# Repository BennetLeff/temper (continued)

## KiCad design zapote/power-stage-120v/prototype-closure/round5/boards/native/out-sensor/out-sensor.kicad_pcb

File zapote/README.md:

# Zapote

**Board checks:** [ERC, DRC and layout command index](CHECKS.md), or
`make -C zapote help`. Includes native current analysis, before/after comparisons,
Rust owners, test evidence, and the current integration/CI checkpoint.

> **Scope on `main` (landed 2026-10-08).** Five maintained units — RTD, current-sense,
> thermal-sense, interlock, gate-drive — plus `power-stage-120v` and the inverter
> measurement framework (superseded by the 120 V stage's own validation plan; see
> `inverter/U3-MEASUREMENT-READINESS.md`). The Rev38 PFC power entry, the voltage-sense unit, the
> PFC-board bridge/shunt FEM and cooling studies, and their crate modules are
> archived at tags `archive/rev38-power-entry-2026-09-25` and
> `archive/zapote-coil-intake-2026-09-25` (see `docs/archive/REV38.md`). Unit
> evidence runs not read by a check also stay in those tags; a unit
> `ACCEPTANCE.md` path that is absent here resolves there. Bulk solver output
> (`*.gz`, `*.npz`, files over 5 MB) is in release `zapote-evidence-2026-10-08`;
> `python3 zapote/tools/evidence_archive.py fetch` restores it in place.

Zapote is Temper's agent engineering subproject centered on a large Rust
validation suite. The working Python/KiCad editing adapter stays in use.

It shares Temper's product inputs and copies needed existing Rust validators
into focused packages such as `zapote-drc` and `zapote-erc`, retaining tests and
provenance. The agent makes placement and routing decisions; Zapote supplies
explicit board edits, engineering feedback, memory, and recorded execution.
See [ARCHITECTURE.md](ARCHITECTURE.md) for package boundaries and
[VALIDATION.md](VALIDATION.md) for the board-validation objective and coverage
ambition. Replacing the Python adapter is deferred.

The [cooker delivery roadmap](https://github.com/BennetLeff/temper/blob/archive/zapote-coil-intake-2026-09-25/docs/plans/2026-09-10-1627-zapote-cooker-roadmap-plan.md)
sets the order from standalone buck/MCU units through the complete routed board and
physical bring-up. Each milestone adds cooker circuitry, Rust validation coverage
and reusable engineering lessons; implementation detail is added as it approaches.

## Current status

Zapote has a standalone Rust workspace with core, DRC, ERC and harness packages.
The [RTD unit](rtd/unit/ACCEPTANCE.md) exercises the source-to-board flow, and
[model qualification](rtd/model-correctness/README.md) checks the meaning of its
passive-network certificates. Device applicability and brownout timing remain
INDETERMINATE; physical tests are NOT RUN.

The [standalone current-sense / primary OCP unit](current-sense/README.md)
adds a separately compiled Atopile source, routed native PCB, corrected
transformer land pattern, bounded electrical model and Rust source/geometry
checks. Its acceptance record separates digital verification from unrun
physical qualification and procurement gaps.

The [standalone voltage-sense / OVP unit](https://github.com/BennetLeff/temper/blob/archive/zapote-coil-intake-2026-09-25/zapote/voltage-sense/README.md) adds the next separately compiled, routed unit, a corrected ADC divider, source-derived electrical checks and saved-document consistency controls. Its digital construction passes while qualification remains explicit.

The [standalone thermal unit](thermal-sense/README.md) adds two external-NTC channels, loaded-feedback trip/release modeling, exact connectivity controls and a routed native PCB. Rev B adds conditional open-wire detection; physical qualification remains separate.

The [isolated gate-drive unit](gate-drive/README.md) has a routed 100 × 80 mm candidate with clean native ERC/DRC and passing Rust construction checks; physical qualification is unrun. The [active PFC power-entry unit](https://github.com/BennetLeff/temper/blob/archive/zapote-coil-intake-2026-09-25/zapote/power-entry/README.md) preserves the 1,800 W nominal AC-input target. Its 54-component, 230 × 210 mm candidate is routed with zero native ERC/DRC findings or unconnected nets and seven passing Rust construction findings. Qualification remains INDETERMINATE. See the [two-board demo](https://github.com/BennetLeff/temper/blob/archive/zapote-coil-intake-2026-09-25/zapote/demo-gate-power/index.html).

The [Rust coverage inventory](validation/inventory-2026-09-12.json) maps Temper donors to Zapote,
lists the checks recorded for each maintained unit, and orders the next ports.
The `zapote-board` CLI checks physical stackup only. The [check index](CHECKS.md)
lists the separate native layout/current and unit electrical-validation commands.

[Engineering memory](https://github.com/BennetLeff/temper/blob/archive/zapote-coil-intake-2026-09-25/zapote/skills/README.md) connects reviewed, versioned lessons to
construction inputs through Rust selection and a thin process transport (the catalog and
Python transport are archived; the Rust policy remains in `zapote-harness`). The
native KiCad adapters live in `harness-lab/`, the generators in `tools/generators/`
and the atopile base library in `elec-base/src`. The old Python
migration outline is superseded by [MIGRATION.md](https://github.com/BennetLeff/temper/blob/archive/zapote-coil-intake-2026-09-25/zapote/MIGRATION.md).

The [Gmsh + Elmer thermal backend](https://github.com/BennetLeff/temper/blob/archive/zapote-coil-intake-2026-09-25/zapote/thermal/README.md) adds a separate external
electrothermal reference path, orchestrated and checked in Rust. Its copper-bar
benchmark establishes solver setup; it does not qualify the power-entry necks
or replace existing board findings.

## Layout

| Path | Purpose |
|---|---|
| `project.toml` | Zapote identity and shared Temper resource map |
| `AGENTS.md` | Local operating rules for work in this project |
| `Makefile` | Rust build/test and common saved-board gates |
| `CHECKS.md` | Check discovery: commands, scope, code owners, evidence and CI status |
| `layout-quality/` | Native geometry/current feedback and supplied-model check catalog |
| `Cargo.toml`, `packages/` | Rust workspace, validators and harness |
| `ports.toml` | Donor hashes, copied tests and extraction changes |
| `validation/` | Dated donor inventory, per-unit coverage and next-port sequence |
| `thermal/` | Gmsh + Elmer backend scope, native installation and reference evidence |
| `ARCHITECTURE.md` | Rust package ownership and agent/validator contract |
| `experiments/` | Experiment definitions and frozen inputs |
| `skills/` | Versioned agent skills and learned artifacts |
| `artifacts/` | Durable evidence manifests and local artifact indexes |
| `runs/` | Git-ignored runtime output |
| `evidence-archive.json` | Manifest of bulk evidence held in release assets; restore with `tools/evidence_archive.py fetch` |
| `docs/` | Design, migration, and operating notes |

## Commands

```sh
make -C zapote setup
make -C zapote help
make -C zapote check
make -C zapote build
```

`setup` checks Rust workspace metadata, `build` builds its binaries/examples,
and `check` runs release Rust tests, native 120 V layout/current analysis, then
the five-unit acceptance runner. Native commands need the KiCad runtimes listed
in [CHECKS.md](CHECKS.md). `check-boards` runs stackup checks only.

Check any new board with `make -C zapote board-check BOARD=/absolute/path/to/board.kicad_pcb`.
The `zapote-board` Rust CLI reads the actual PCB bytes, hashes them and runs
`DRC.BOARD.STACKUP`; its pass is not a substitute for unit electrical checks
or native ERC/DRC. Register new maintained unit paths in `UNIT_BOARDS` before
acceptance. Historical/frozen artifacts are not modified by these commands.
Legacy buck `qualify-buck` and `engineering` commands remain explicitly delegated.

## Direction

Zapote is not another PCB optimizer. It is the harness layer that makes agent
behavior measurable, repeatable, inspectable, and improvable across Temper's
engineering domains. See `MIGRATION.md` for the planned boundary and the
current source-of-truth decisions.

The [standalone interlock](interlock/README.md) adds seven fault inputs, watchdog/liveness gating and a stateful reset latch. Its source-driven Rust checks evaluate 4,096 gate/state/clock combinations and reject physical connectivity and model mutations. Sensor-liveness production and receiver behavior remain integration obligations.

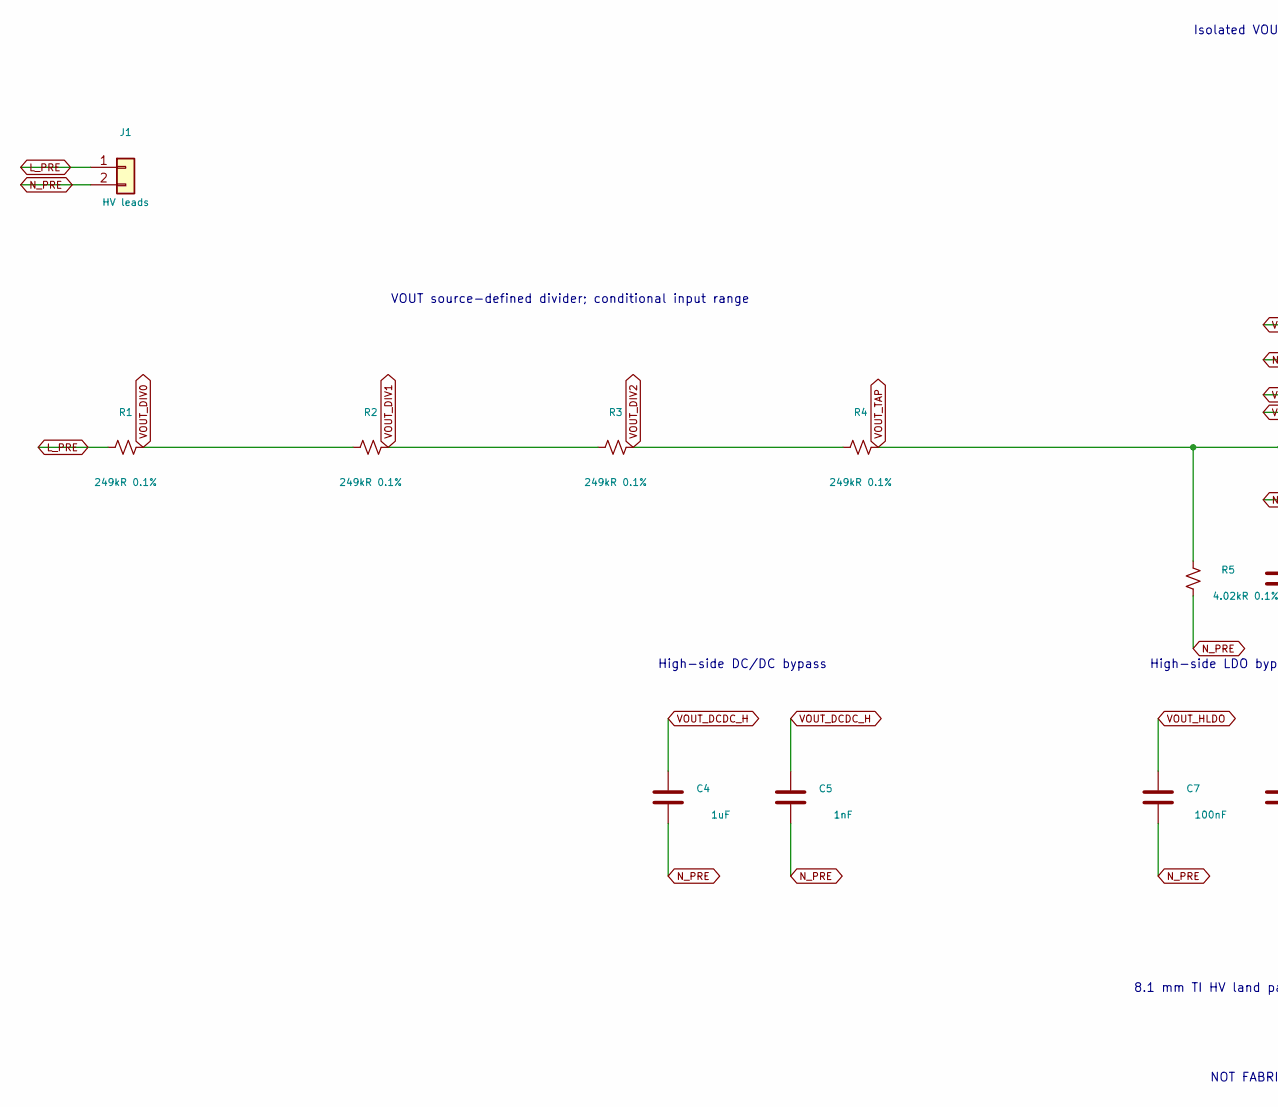
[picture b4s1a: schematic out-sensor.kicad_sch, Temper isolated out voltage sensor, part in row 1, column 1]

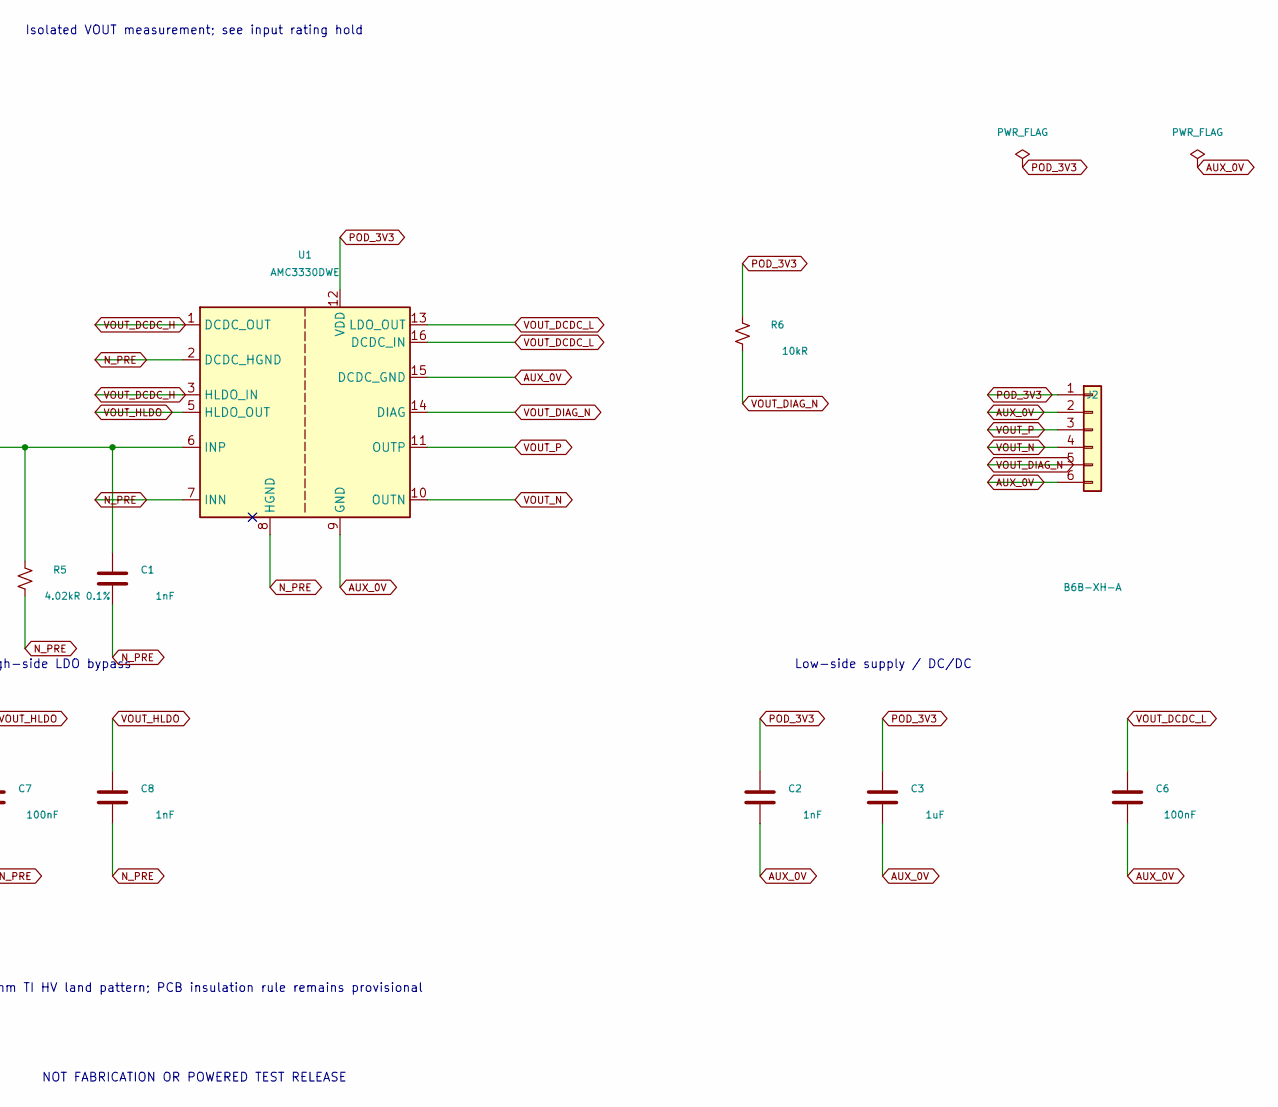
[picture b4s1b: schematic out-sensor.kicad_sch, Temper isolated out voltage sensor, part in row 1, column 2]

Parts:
C1: 1nF; C_0603_1608Metric; MPN 1nF C0603C102J5GACTU
C2: 1nF; C_1206_3216Metric; MPN 1nF 12065C102KAT2A
C3: 1uF; C_1206_3216Metric; MPN 1uF 12063C105KAT2A
C4: 1uF; C_0603_1608Metric; MPN 1uF CGA3E1X7R1E105K080AC
C5, C8: 1nF; C_0603_1608Metric; MPN 1nF C0603C102K5RACTU
C6, C7: 100nF; C_0603_1608Metric; MPN 100nF C0603C104K5RACAUTO
J1: HV leads; HV_WirePair_P25; MPN HV_SOLDER_LEADS_WITH_EXTERNAL_STRAIN_RE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
J2: B6B-XH-A; JST_XH_B6B-XH-A_1x06_P2.50mm_Vertical; MPN B6B-XH-A(LF)(SN)
R1, R2, R3, R4: 249kR 0.1%; R_1206_3216Metric; MPN TNPW1206249KBEEA 249kR 0.1%
R5: 4.02kR 0.1%; R_1206_3216Metric; MPN TNPW12064K02BEEA 4.02kR 0.1%
R6: 10kR; R_0603_1608Metric; MPN 10kR CRCW060310K0FKEA
U1: AMC3330DWE; AMC3330_DWE_HV; MPN AMC3330DWE

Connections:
AUX_0V: C2.2, C3.2, C6.2, J2.2, J2.6, U1.9 (GND), U1.15 (DCDC_GND)
L_PRE: J1.1, R1.1
N_PRE: C1.2, C4.2, C5.2, C7.2, C8.2, J1.2, R5.2, U1.2 (DCDC_HGND), U1.7 (INN), U1.8 (HGND)
POD_3V3: C2.1, C3.1, J2.1, R6.1, U1.12 (VDD)
VOUT_DCDC_H: C4.1, C5.1, U1.1 (DCDC_OUT), U1.3 (HLDO_IN)
VOUT_DCDC_L: C6.1, U1.13 (LDO_OUT), U1.16 (DCDC_IN)
VOUT_DIAG_N: J2.5, R6.2, U1.14 (DIAG)
VOUT_DIV0: R1.2, R2.1
VOUT_DIV1: R2.2, R3.1
VOUT_DIV2: R3.2, R4.1
VOUT_HLDO: C7.1, C8.1, U1.5 (HLDO_OUT)
VOUT_N: J2.4, U1.10 (OUTN)
VOUT_P: J2.3, U1.11 (OUTP)
VOUT_TAP: C1.1, R4.2, R5.1, U1.6 (INP)

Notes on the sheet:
VOUT source-defined divider; conditional input range
Isolated VOUT measurement; see input rating hold
8.1 mm TI HV land pattern; PCB insulation rule remains provisional
High-side DC/DC bypass
High-side LDO bypass
Low-side supply / DC/DC
NOT FABRICATION OR POWERED TEST RELEASE

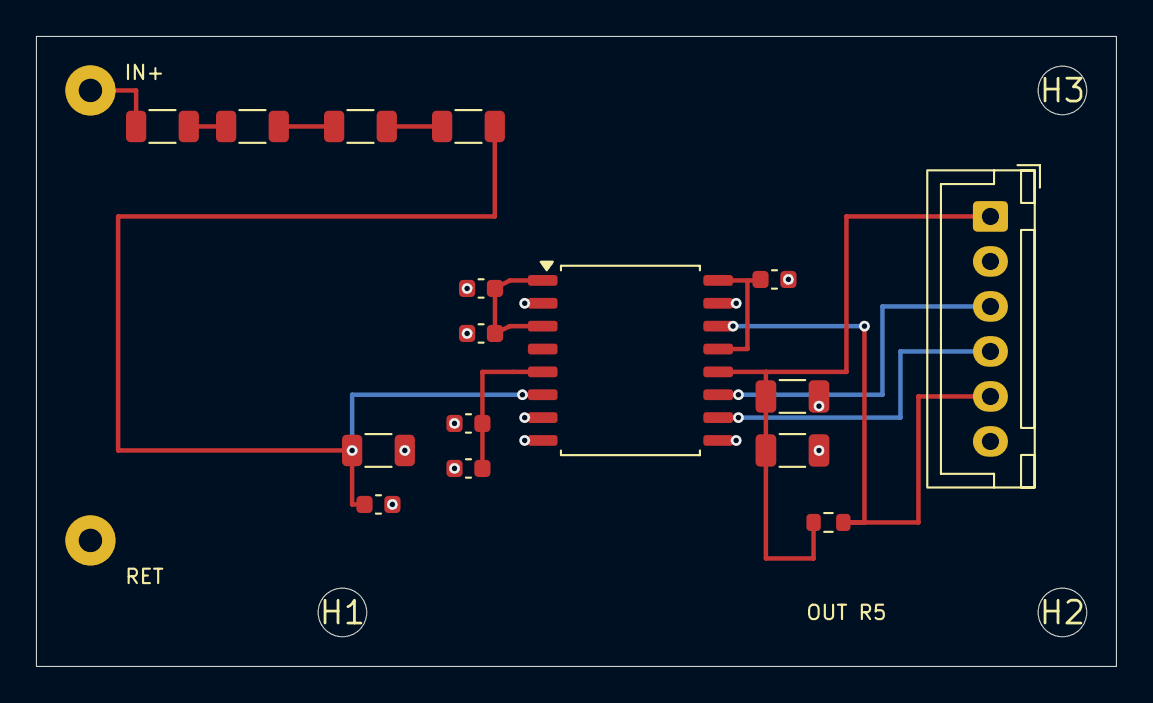
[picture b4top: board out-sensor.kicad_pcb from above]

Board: 2 copper layers, 60.0 x 35.0 mm, 20 parts (0 on the bottom side), 14 nets.

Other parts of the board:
H1, H2, H3: (no value)

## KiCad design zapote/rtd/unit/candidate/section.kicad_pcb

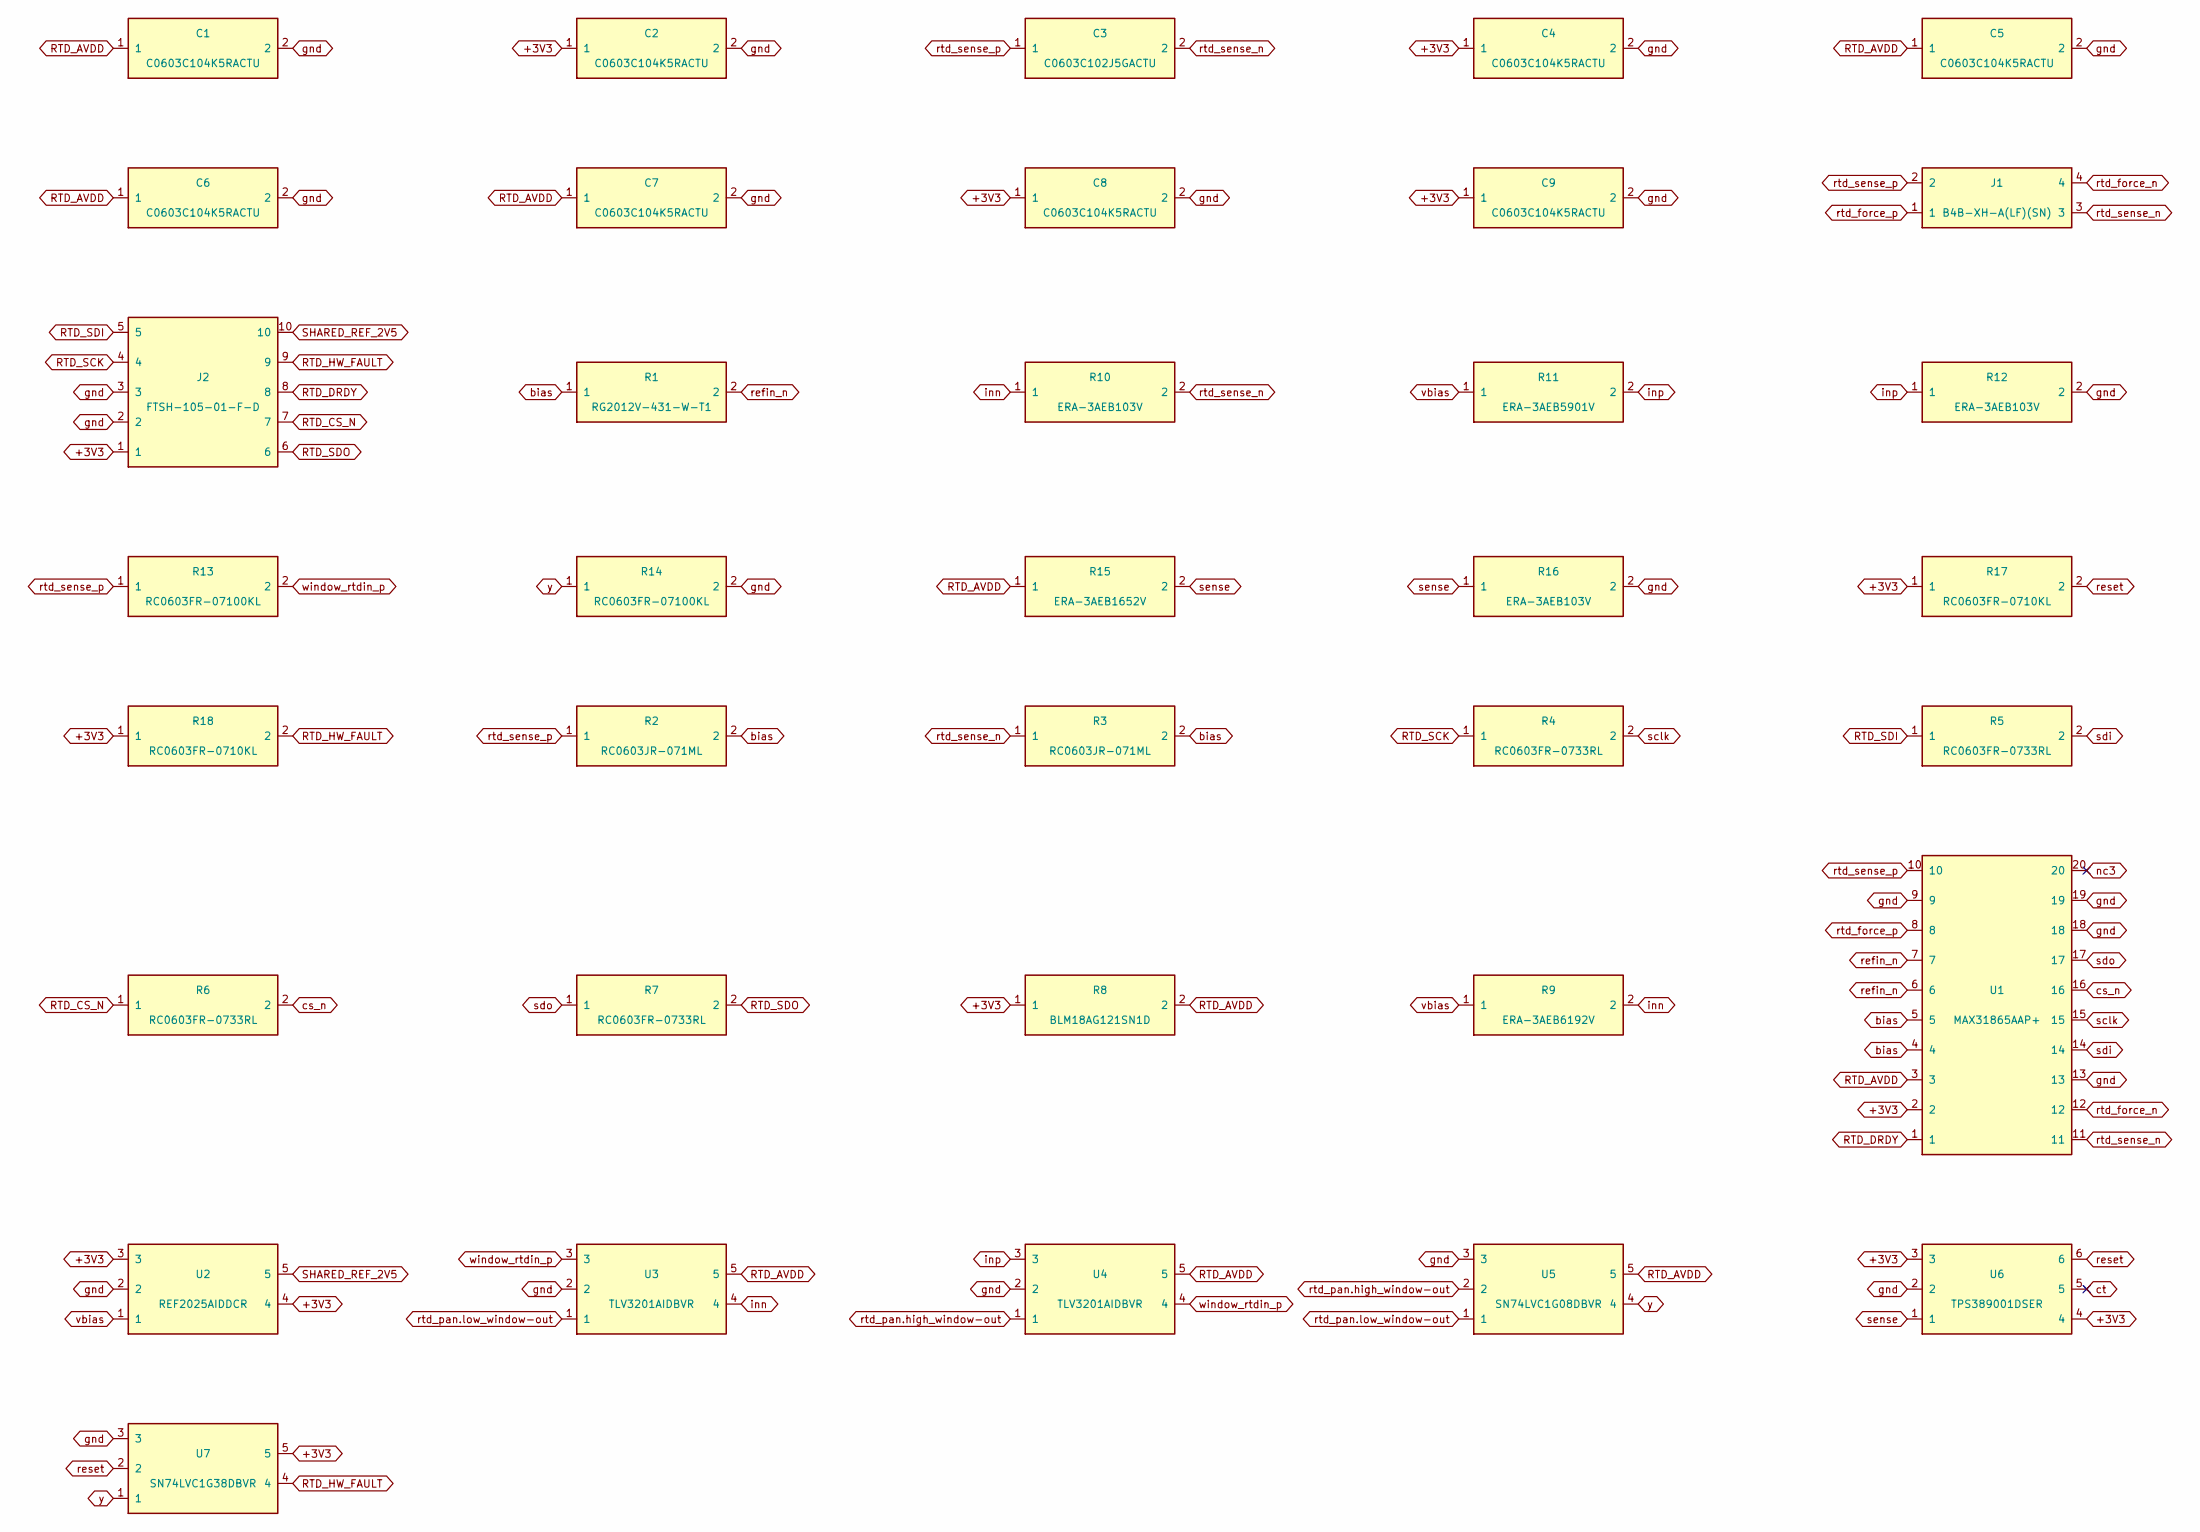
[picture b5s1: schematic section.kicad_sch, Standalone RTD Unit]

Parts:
C1, C2, C4, C5, C6, C7, C8, C9: C0603C104K5RACTU; C_0603_1608Metric
C3: C0603C102J5GACTU; C_0603_1608Metric
J1: B4B-XH-A(LF)(SN); JST_XH_B4B-XH-A_1x04_P2.50mm_Vertical
J2: FTSH-105-01-F-D; FTSH-105-01-F-D_2x5_P1.27mm
R1: RG2012V-431-W-T1; R_0805_2012Metric
R2, R3: RC0603JR-071ML; R_0603_1608Metric
R4, R5, R6, R7: RC0603FR-0733RL; R_0603_1608Metric
R8: BLM18AG121SN1D; L_0603_1608Metric
R9: ERA-3AEB6192V; R_0603_1608Metric
R10, R12, R16: ERA-3AEB103V; R_0603_1608Metric
R11: ERA-3AEB5901V; R_0603_1608Metric
R13, R14: RC0603FR-07100KL; R_0603_1608Metric
R15: ERA-3AEB1652V; R_0603_1608Metric
R17, R18: RC0603FR-0710KL; R_0603_1608Metric
U1: MAX31865AAP+; SSOP-20_3.9x8.7mm_P0.635mm
U2: REF2025AIDDCR; SOT-23-5
U3, U4: TLV3201AIDBVR; SOT-23-5
U5: SN74LVC1G08DBVR; SOT-23-5
U6: TPS389001DSER; TPS389001DSER_WSON-6_DSE
U7: SN74LVC1G38DBVR; SOT-23-5

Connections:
+3V3: C2.1, C4.1, C8.1, C9.1, J2.1, R8.1, R17.1, R18.1, U1.2, U2.3, U2.4, U6.3, U6.4, U7.5
RTD_AVDD: C1.1, C5.1, C6.1, C7.1, R8.2, R15.1, U1.3, U3.5, U4.5, U5.5
RTD_CS_N: J2.7, R6.1
RTD_DRDY: J2.8, U1.1
RTD_HW_FAULT: J2.9, R18.2, U7.4
RTD_SCK: J2.4, R4.1
RTD_SDI: J2.5, R5.1
RTD_SDO: J2.6, R7.2
SHARED_REF_2V5: J2.10, U2.5
bias: R1.1, R2.2, R3.2, U1.4, U1.5
cs_n: R6.2, U1.16
ct: U6.5
gnd: C1.2, C2.2, C4.2, C5.2, C6.2, C7.2, C8.2, C9.2, J2.2, J2.3, R12.2, R14.2, R16.2, U1.9, U1.13, U1.18, U1.19, U2.2, U3.2, U4.2, U5.3, U6.2, U7.3
inn: R9.2, R10.1, U3.4
inp: R11.2, R12.1, U4.3
nc3: U1.20
refin_n: R1.2, U1.6, U1.7
reset: R17.2, U6.6, U7.2
rtd_force_n: J1.4, U1.12
rtd_force_p: J1.1, U1.8
rtd_pan.high_window-out: U4.1, U5.2
rtd_pan.low_window-out: U3.1, U5.1
rtd_sense_n: C3.2, J1.3, R3.1, R10.2, U1.11
rtd_sense_p: C3.1, J1.2, R2.1, R13.1, U1.10
sclk: R4.2, U1.15
sdi: R5.2, U1.14
sdo: R7.1, U1.17
sense: R15.2, R16.1, U6.1
vbias: R9.1, R11.1, U2.1
window_rtdin_p: R13.2, U3.3, U4.4
y: R14.1, U5.4, U7.1

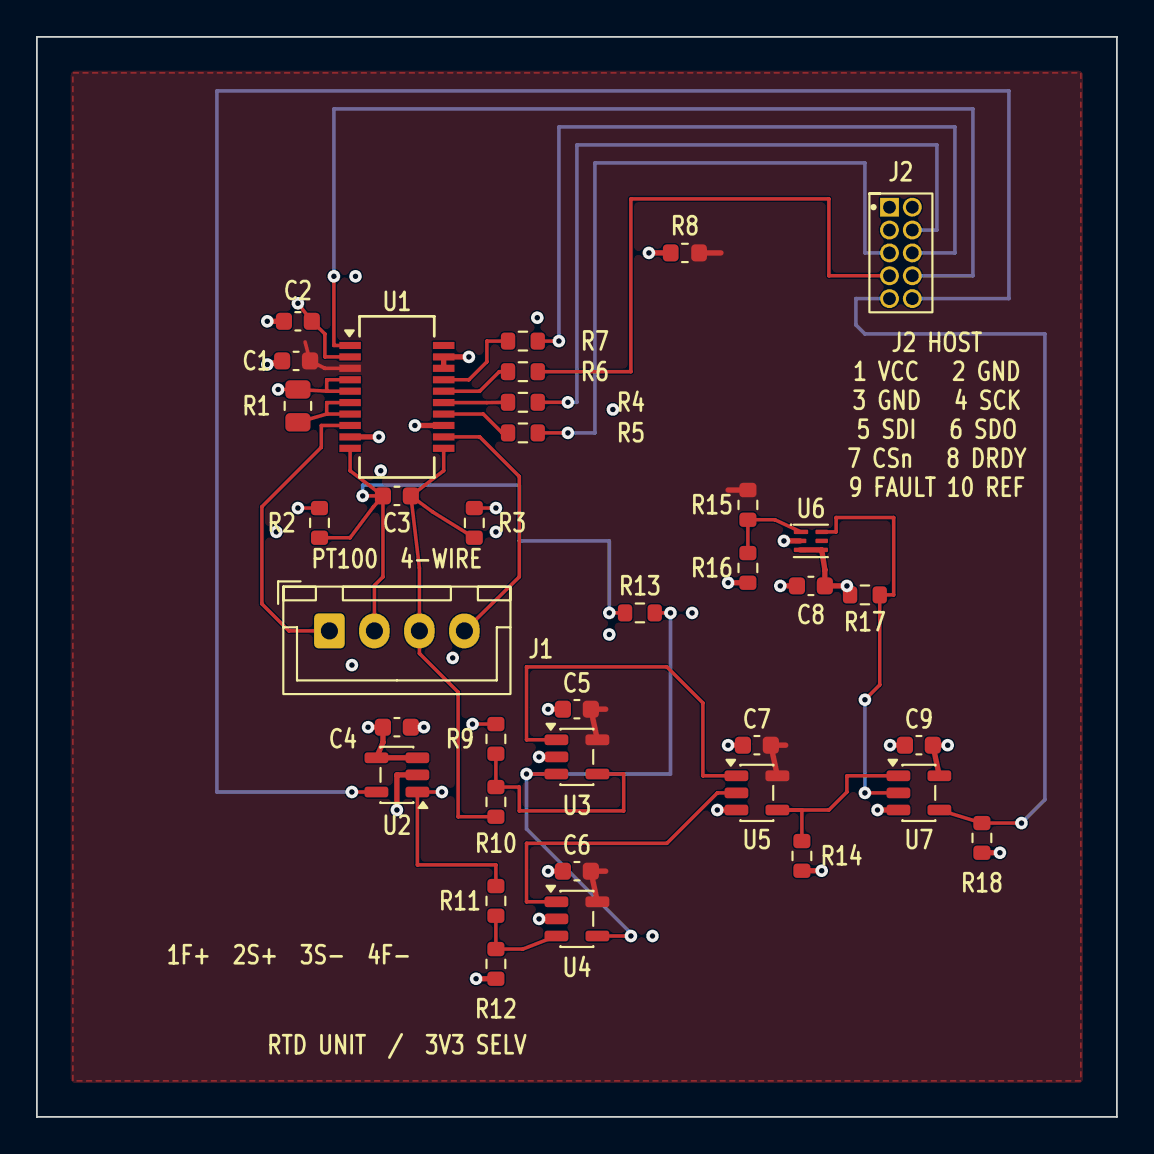
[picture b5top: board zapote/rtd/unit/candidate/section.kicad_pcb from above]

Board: 4 copper layers, 60.0 x 60.0 mm, 36 parts (0 on the bottom side), 29 nets.

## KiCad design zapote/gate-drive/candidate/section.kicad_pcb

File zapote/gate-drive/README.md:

# Standalone isolated dual gate drive

This unit is source-owned by `elec/src/gate_drive_unit.ato` and is compiled
through Atopile 0.2.69. The selected driver is TI UCC21550BDWKR, the
orderable tape-and-reel suffix for the verified DWK 14-pin package. Its
physical pins are 1–11 and 14–16; pins 12 and 13 are absent.

The control boundary is J1 (PWM_H, PWM_L, PERMIT, CTRL_GND). J2 is the one
externally provided isolated 15 V low-side supply and HV_RETURN boundary.
The high-side supply is a bootstrap from that floating rail through D1 and
C4, referenced to the high-side Kelvin return. J3 and J4 expose gate/Kelvin-
return pairs; HV_RETURN is carried by J2 and J4. Q1 (AO3400A, exact
1=G/2=S/3=D map) is the source-level PERMIT inverter, with a 100 kΩ gate
pulldown and 10 kΩ DIS pullup.
No control return is tied to HV_RETURN, and no local transformer or DC/DC is
claimed.

`source-build-09/` is the current successful source compile/export. The final
routed board is `candidate/section.kicad_pcb`, with route08, native extraction,
Rust construction checks, and native ERC/DRC receipts retained under
`evidence/`. The Edge.Cuts centreline is exactly 100 mm by 80 mm; its 0.10 mm
stroke makes the measured outer bounding box 100.10 mm by 80.10 mm. D1 is the
exact Vishay UF4007-E3/54 DO-41 through-hole
part. U1 uses a labeled, low-fidelity 14-lead DWK visualization; its physical
pins are 1–11 and 14–16. This is not a mechanical qualification model.

The validated construction contract uses one externally provided isolated
15 V low-side supply at J2 and a bootstrap high-side supply. The 39 kOhm DT
resistor is a conditional interpolation envelope, not a published TI timing
guarantee. Bootstrap startup, loaded switching, thermal behavior, and timing
measurement remain unrun.

Selected memory notes used: `rtd-mem-001`, `current-sense-mem-001`,
`voltage-sense-mem-001`, `thermal-sense-mem-001`, `thermal-sense-mem-002`,
and `interlock-mem-001`. Their procedural effect was to keep model claims
separate from physical qualification, verify exact package geometry and pin
names, preserve domain-specific returns, and read nested native ERC findings.

Source SHA-256 and compiled artifact hashes are recorded in
`source-build-09/build-receipt.json` and `evidence/native-09.json`.

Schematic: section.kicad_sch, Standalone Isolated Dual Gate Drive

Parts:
C1, C2: C0603C104K5RACTU; C_0603_1608Metric
C3, C4: GRM32ER71H106KA12L; C_1210_3225Metric
D1: UF4007-E3/54; D_DO-41_SOD81_P10.16mm_Horizontal
J1: B4B-XH-A(LF)(SN); JST_XH_B4B-XH-A_1x04_P2.50mm_Vertical
J2, J3, J4, J5: 61300211121; PinHeader_1x02_P2.54mm_Vertical
Q1: AO3400A; SOT-23
R1: RC0603FR-071KL; R_0603_1608Metric
R2: RC0603FR-07100KL; R_0603_1608Metric
R3: RC0603FR-0710KL; R_0603_1608Metric
R4: RC0603FR-0739KL; R_0603_1608Metric
R5, R7: RC1206FR-073R9L; R_1206_3216Metric
R6, R8: RC0603FR-072K2L; R_0603_1608Metric
U1: UCC21550BDWKR; SOIC16W_Isolated

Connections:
ctrl_gnd: C1.2, J1.4, J5.2, Q1.2 (S), R2.2, R4.2, U1.4 (GNDI)
dis: Q1.3 (D), R3.1, U1.5 (DIS)
dt: R4.1, U1.6 (DT)
g: Q1.1 (G), R1.2, R2.1
gate_h_kelvin: C4.2, J3.2, R6.2, U1.14 (VSSA)
gate_h_out: J3.1, R5.2, R6.1
gate_l_kelvin: C2.2, C3.2, J2.2, J4.2, R8.2, U1.9 (VSSB)
gate_l_out: J4.1, R7.2, R8.1
nc_7: U1.7 (NC_7)
outa: R5.1, U1.15 (OUTA)
outb: R7.1, U1.10 (OUTB)
permit: J1.3, R1.1
pwm_h: J1.1, U1.1 (INA)
pwm_l: J1.2, U1.2 (INB)
v3v3: C1.1, J5.1, R3.2, U1.3 (VCCI_1), U1.8 (VCCI_2)
v15_ls: C2.1, C3.1, D1.2, J2.1, U1.11 (VDDB)
vdda: C4.1, D1.1, U1.16 (VDDA)

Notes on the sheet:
CONTROL / J1: PWM_H, PWM_L, PERMIT, CTRL_GND
ISOLATED LS SUPPLY / J2: +15V_LS, HV_RETURN
GATE OUTPUTS / J3,J4: GATE + KELVIN RETURN
Q1 AO3400A: PERMIT high pulls DIS low; floating PERMIT is disabled

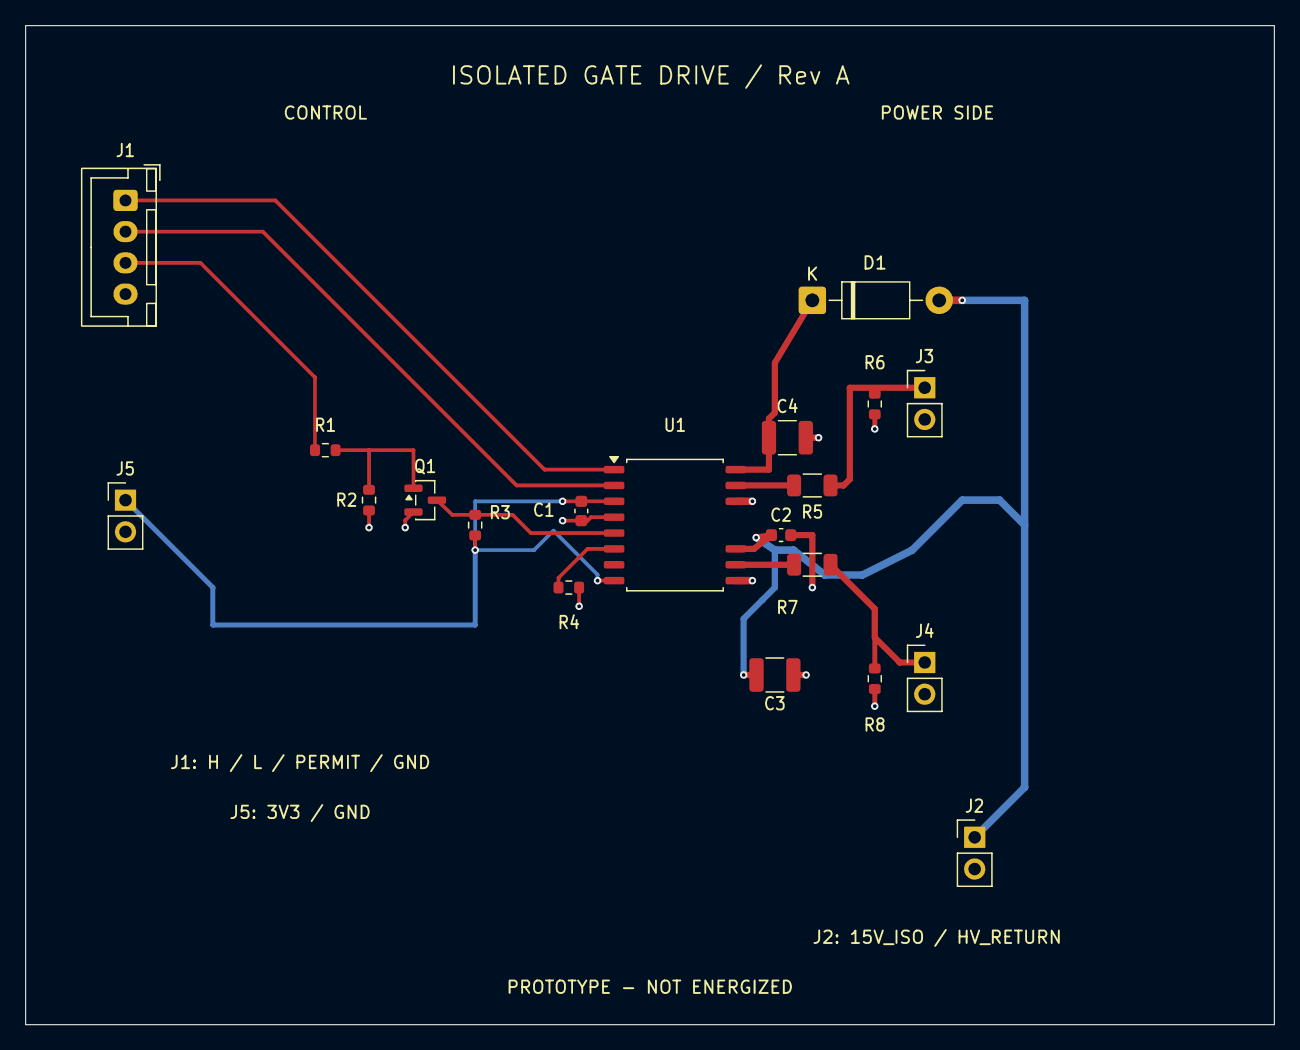
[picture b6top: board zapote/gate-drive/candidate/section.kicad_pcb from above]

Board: 2 copper layers, 100.0 x 80.0 mm, 20 parts (0 on the bottom side), 16 nets.

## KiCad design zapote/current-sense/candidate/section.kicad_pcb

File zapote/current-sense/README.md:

# Standalone current-sensing / primary OCP unit

The native project is `candidate/section.kicad_pro`, with schematic `candidate/section.kicad_sch` and routed board `candidate/section.kicad_pcb`. The Atopile entry is `elec/src/current_sense_unit.ato:CurrentSenseUnit`. This is a separate 21-component unit, not an integrated cooker board.

The board is 80 × 83 mm with two copper layers. A CST3015 transformer senses AC primary current; a floating burden and biased comparator pair detect either polarity and produce an active-high fault. See [INTERFACES.md](INTERFACES.md) for exact pins, host obligations and qualification steps, and [bom/README.md](bom/README.md) for exact parts and purchasing gaps.

## Build and evidence

- `source-build-04/`: pinned Atopile compilation and exported component/net identities.
- `generated-04/`: strict source-derived native generation at the authored final component poses. Its generated board is an unrouted provenance artifact, not the deliverable PCB.
- `candidate/`: final routed native project and source manifest.
- `poses.json`, `routes-*.json`, `edits-*.json`, `labels-*.json`, `outline-final.json`: explicit agent decisions, replayed through thin native adapters. No placement or routing search algorithm was invoked for this unit.
- `evidence/`: retained failures, native check reports, source equality oracle, renders, footprint review and final validation receipts.
- `circuit/`: Luna's bounded analytical model and supporting proposal documents. The canonical compiled source and [INTERFACES.md](INTERFACES.md) govern final native references; the separately retained `.ato` proposal is not a second build entry.
- `memory/`: actual selected context and reported use for this attempt, plus preparation-only validation of the next reviewed memory revision.

The source manifest describes generation inputs and its generated board hash. It must not be mistaken for the final routed-board hash. The final acceptance receipt binds the routed board, native extraction, model, Rust executable and check results separately.

## What this experiment established

The full Atopile → strict native generation → agent placement/routing → native checks path produced a connected standalone board. Native ERC and DRC/parity reports are retained rather than summarized without inputs. The Rust harness adds source/model binding and explicit geometry/electrical checks with negative controls; the acceptance record states their actual outcome and limits.

The inherited transformer footprint did not match the official land pattern. The corrected local footprint and independent native readback are documented in [the durable learning](../../docs/solutions/logic-errors/cst3015-land-pattern-edge-gap.md). The old full-cooker circuit and shared legacy footprint remain separate migration work.

The inherited bias topology could not establish the claimed midpoint. The standalone design uses a floating burden around a separately bypassed midpoint. Model review then corrected a load-current sign error and included the actual series-resistor tolerance. These are functional findings, not cosmetic routing changes.

## Qualification boundary

The model calculates an approximately 50.12 A nominal trip, with a conditional 46.18–54.16 A corner band. It is a static circuit calculation driven by an ideal transformer transfer relation for an AC waveform; it does not claim that a current transformer senses DC. CT transfer/frequency effects, unspecified hysteresis, hot leakage, startup/brownout, complete shutdown timing, primary termination temperature and assembled insulation remain unqualified. Overall physical acceptance remains INDETERMINATE and all hardware tests are NOT RUN.

This delivers a routed unit and an exercised validation harness. It is not a fabrication or energized-use approval. Exact comparator/clamp availability also remains open. The next physical step is a separately reviewed isolated unit test fixture; full-cooker integration follows individual unit qualification.

The 2026-09-11 [stackup repair](evidence/stackup-fix/README.md) supersedes the original physical stackup: 1.44 mm core / 1.60 mm total, guarded by Rust. The canonical PCB path is unchanged. [Updated 3D render](evidence/stackup-fix/after.png).

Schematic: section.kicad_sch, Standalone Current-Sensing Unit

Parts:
C1, C2: GRM31C5C1H104JA01L; C_1206_3216Metric
C3, C4, C5: C0603C104K5RACTU; C_0603_1608Metric
D1, D2: BAT54H,115; D_SOD-123F
J1: NON_PURCHASED_BARE_LANDS; LitzPad_15A
J2: B4B-XH-A(LF)(SN); JST_XH_B4B-XH-A_1x04_P2.50mm_Vertical
R1: RC1206FR-071R5L; R_1206_3216Metric
R2, R3: ERA3AEB102V; R_0603_1608Metric
R4: RC1206FR-071KL; R_1206_3216Metric
R5, R8: ERA3AEB3741V; R_0603_1608Metric
R6, R7: ERA3AEB103V; R_0603_1608Metric
T1: CST3015-100ED; CST3015_Datasheet2025
U1, U2: TLV3201AIDBVR; SOT-23-5
U3: CD74HC4075M96; SOIC-14_3.9x8.7mm_P1.27mm

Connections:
+3V3: C3.1, C4.1, C5.1, D1.1, J2.1, R2.1, R5.1, R7.1, U1.5, U2.5, U3.14
CT_SENSE: C1.1, R1.1, R4.1, T1.3
OCP_FAULT: J2.3, U3.9
OCP_NEG: U2.1, U3.2
OCP_POS: U1.1, U3.1
PRIMARY_IN: J1.1, T1.1
PRIMARY_OUT: J1.2, T1.2
REF_HI: R5.2, R6.1, U1.4
REF_LO: R7.2, R8.1, U2.3
SENSE_MON: D1.2, D2.1, J2.4, R4.2, U1.3, U2.4
VBIAS: C1.2, C2.1, R1.2, R2.2, R3.1, T1.4
gnd: C2.2, C3.2, C4.2, C5.2, D2.2, J2.2, R3.2, R6.2, R8.2, U1.2, U2.2, U3.3, U3.4, U3.5, U3.7, U3.8, U3.11, U3.12, U3.13
y2: U3.6
y3: U3.10

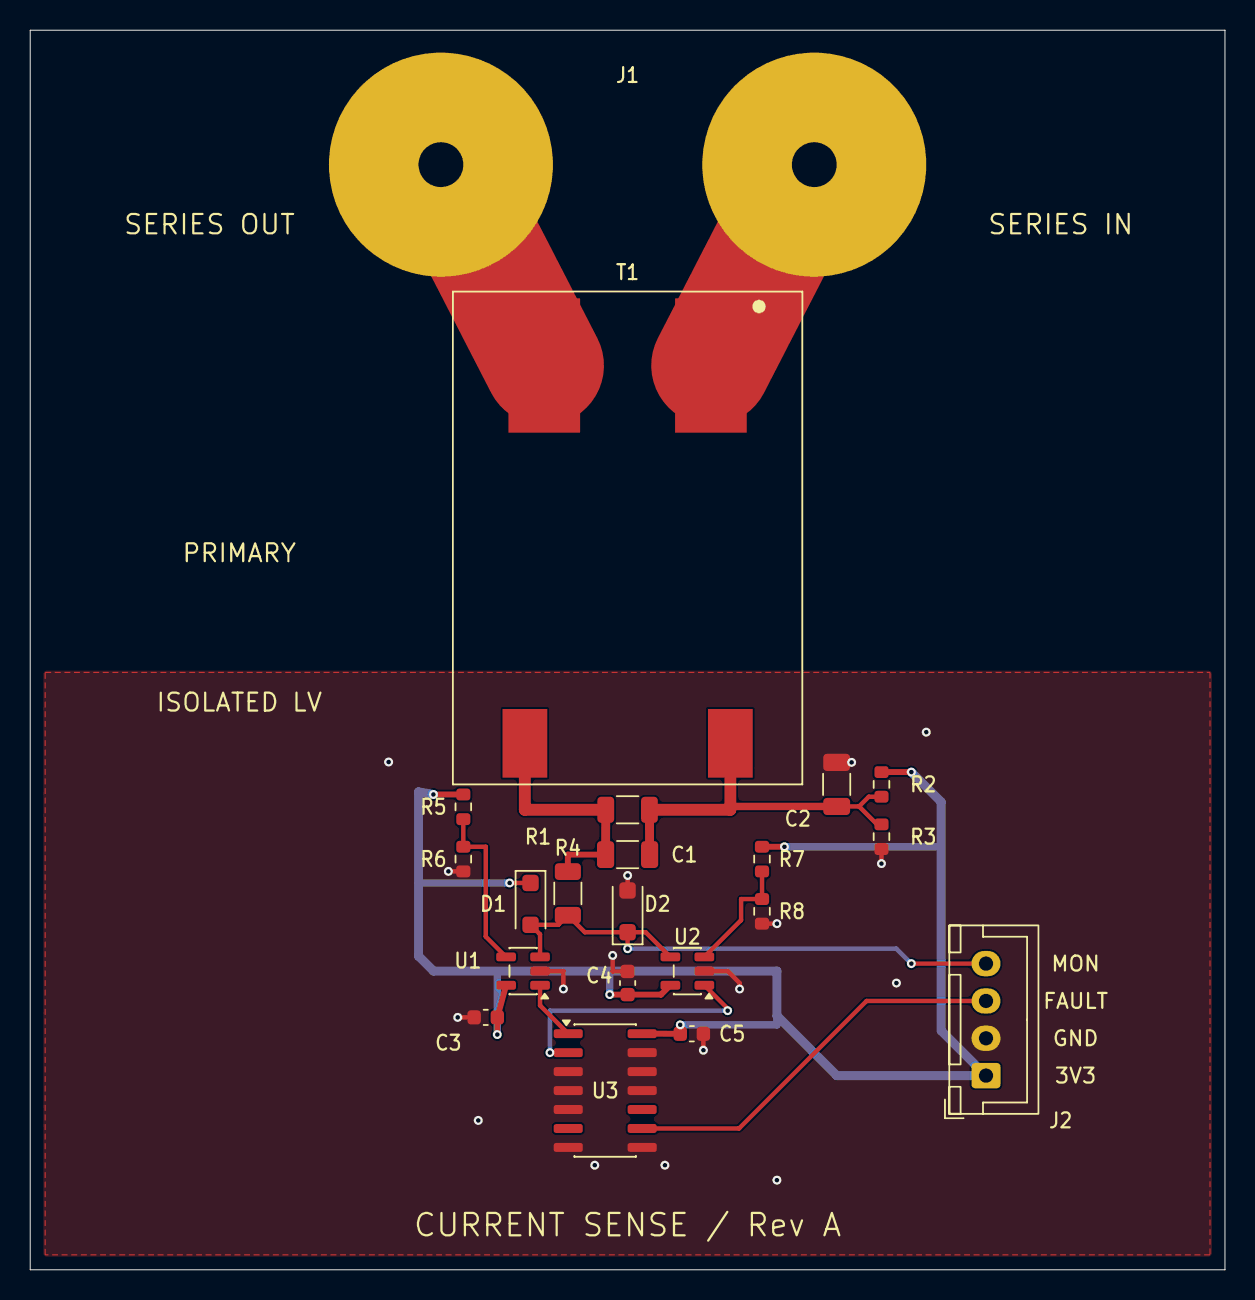
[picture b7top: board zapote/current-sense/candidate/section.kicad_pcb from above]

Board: 2 copper layers, 80.0 x 83.0 mm, 21 parts (0 on the bottom side), 12 nets.

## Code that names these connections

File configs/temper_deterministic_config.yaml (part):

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  grid_alignment: true

# Component spacing constraints
# The 'tier' field determines if a constraint is hard (filter rejects) or soft (scorer penalizes)
minimum_spacing:
  # Hard constraint: High-power MOSFETs must be separated for thermal management
  - components: ["Q1", "Q2"]
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        max_distance_mm: 20.0
        tier: "soft"

# EXP-11: Signal-to-HV clearance constraints for gate drive routing
# These ensure gate driver outputs are placed close enough to MOSFET gates
# that signal routes don't need to pass near HV pins (6mm IEC 60335 creepage)
signal_hv_clearances:
  - name: "gate_h_clearance"
    signal_component: "U_GATE"
    signal_pin: "15"          # OUTA (high-side gate output)
    target_component: "Q1"
    target_pin: "1"           # Gate pin
    hv_component: "Q1"
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
  - name: "gate_l_clearance"
    signal_component: "U_GATE"
    signal_pin: "10"          # OUTB (low-side gate output)
    target_component: "Q2"
    target_pin: "1"           # Gate pin
    hv_component: "Q2"
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placement_proximity:
  - name: "ugate_to_rgateh"
    from_component: "U_GATE"
    from_pin: "15"            # OUTA
    to_component: "R_GATE_H"
    to_pin: "1"
    max_distance_mm: 12.0
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
  - name: "ugate_to_rgatel"
    from_component: "U_GATE"
    from_pin: "10"            # OUTB
    to_component: "R_GATE_L"
    to_pin: "1"
    max_distance_mm: 12.0
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
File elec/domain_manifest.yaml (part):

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                             # (Sec 7).
      - input                # ADDED (this change): traced from the freshly
                             # compiled netlist -- net contains U6.10
                             # (UCC21550 pin 10 = OUTB, `components.ato`'s
                             # own "# Secondary side" pin group, the SAME
                             # isolator "secondary" group already declared
                             # below for `hb.gate_hs.driver` -- VSSB/OUTB/
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                                # catch exactly that and did.
      - discharge.k_dis1-coil1  # discharge.k_dis1's own declared "coil"
                                # group (below), pin_labels already call
                                # both coil pins "SELV coil drive" -- listed
                                # here too so the domain check and the
                                # isolator check (below) do not disagree
                                # about the same two pins' domain. See
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                             # (override_net_name applied at main.ato:835,
                             # `ct_sense.i_sense.line.override_net_name =
                             # "I_SENSE"`). The isolator entry below already
                             # declares ct_sense.ct's pins 3/4 (S1/S2) as its
                             # own "secondary" group -- correctly modeling
                             # the component's barrier -- but the compiled
                             # NET this pin sits on was never added to this
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                             # Traced directly from the compiled netlist
                             # (elec/build/default.net, net code 117): T2.3
                             # (ct.S1), U19.3 (safety.ocp2.comp, the
                             # TLV3201's INP pin), C37.1 (safety.ocp2.
                             # c_filter), R65.1 (safety.ocp2.r_burden) are
                             # all on this net. Genuinely SELV, identical
                             # isolation construction to `I_SENSE` above:
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                             # violations in practice"), so all four interior
                             # nodes sit in the SAME connected component as
                             # the already-verified-SELV far end
                             # (comp.INP/V_BUS_SENSE) -- domain-labeling them
                             # HV asserts two domains for one connected
                             # component, which the disjointness check
                             # correctly rejects. That is the real,
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  # crossing) ---
  # Same standard clause and PE-bonded-earth reasoning as the comparator
  # divider above -- not repeated in full here. This divider feeds
  # mcu.adc_v_bus (V_BUS_SENSE, SELV) rather than the comparator's INP pin.
  #
  # CONSTRUCTION DEFECT FOUND AND FIXED (2026-07-26, this same change): this
  # divider was PREVIOUSLY a single 510k resistor (r_adc_top) in series with
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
